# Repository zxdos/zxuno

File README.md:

# uGoph - gopher client for ZX-Uno(and possible other zx-spectrums)

## Requirements

For running you need:
 * ZX-Uno(or compatible) zx-spectrum clone with UART core
 * Stored WiFi creds via [.iwconfig](https://github.com/nihirash/iwconfig) utility.

For development you need only sjasmplus. 

Sadly, but there no emulator with ZX-Uno's UART.

## Supported features

Current version supports:

 * Rendering gopher-pages(catalogs)
 * Navigation between pages and servers
 * Rendering plain-text pages
 * Downloading binary files to SD card
 * Opening specified server(only by root path)

## Legals

(c) 2019 Alexander Sharikhin

This program is free software: you can redistribute it and/or modify
it under the terms of the GNU General Public License as published by
the Free Software Foundation, either version 3 of the License, or
(at your option) any later version.

This program is distributed in the hope that it will be useful,
but WITHOUT ANY WARRANTY; without even the implied warranty of
MERCHANTABILITY or FITNESS FOR A PARTICULAR PURPOSE.  See the
GNU General Public License for more details.

You should have received a copy of the GNU General Public License
along with this program.  If not, see <https://www.gnu.org/licenses/>.

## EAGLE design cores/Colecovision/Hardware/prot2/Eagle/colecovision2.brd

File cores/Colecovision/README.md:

# colecofpga
Colecovision FGPA port from old PACE project.

The original project information is here:
http://members.iinet.net.au/~msmcdoug/pace/Nanoboard/nanoboard.html

This project is a ColecoFPGA design port to the Terasic DE-1 and DE-2 development boards, ZX-Uno board and a stand-alone version with a EP2C5 Chinese board.

The Hardware folder is the Eagle project for the prototype. In Synth folder there are projects for all cards. The prototype 1 did not work and is abandoned, the project with the EP4C10 card is not completed.

The second prototype use SNES control to emulate all of the original joystick buttons. Holding TL button the original buttons simulate:

<pre>
Y      => 1
X      => 2
B      => 3
A      => 4
SELECT => 5
START  => 6
</pre>

Holding TR button the original buttons simulate:

<pre>
Y      => 7
X      => 8
B      => 9
A      => 0
SELECT => *
START  => #
</pre>

Holding START and SELECT together resets the machine, returning in the multcart menu.

The B button and Y (auto-fire) is the fire 1 of original joystick. The A button and X (auto-fire) is the fire 2.

For the DE-1, DE-2 and ZX-Uno boards the PS/2 keyboard emulates the original joystick:

The arrow keys simulate the original directional. Z key is the 'fire 1', X key is 'fire 2', 0-9 is '0-9', Q key is '*' and W key is '#'. ESC key resets the machine. For the ZX-Uno the joystick port also works for directionals and fire 1.

The key combination CTRL+ALT+BACKSPACE, on ZX-Uno version, reloads the main core of Xilinx, returning to the main menu.

In boards with VGA output (ZX-Uno), uses the HOME key to toggle VGA output.

In this circuit the BIOS ROM is loaded from the SD card as well as the ROM multcart. In the source folder 'SD_Card' contains all necessary files to the SD card. Format it to FAT16 and copy the files.

In multcart menu, use the directionals to navigate the ROMs and use FIRE 1 button to load the selected ROM.

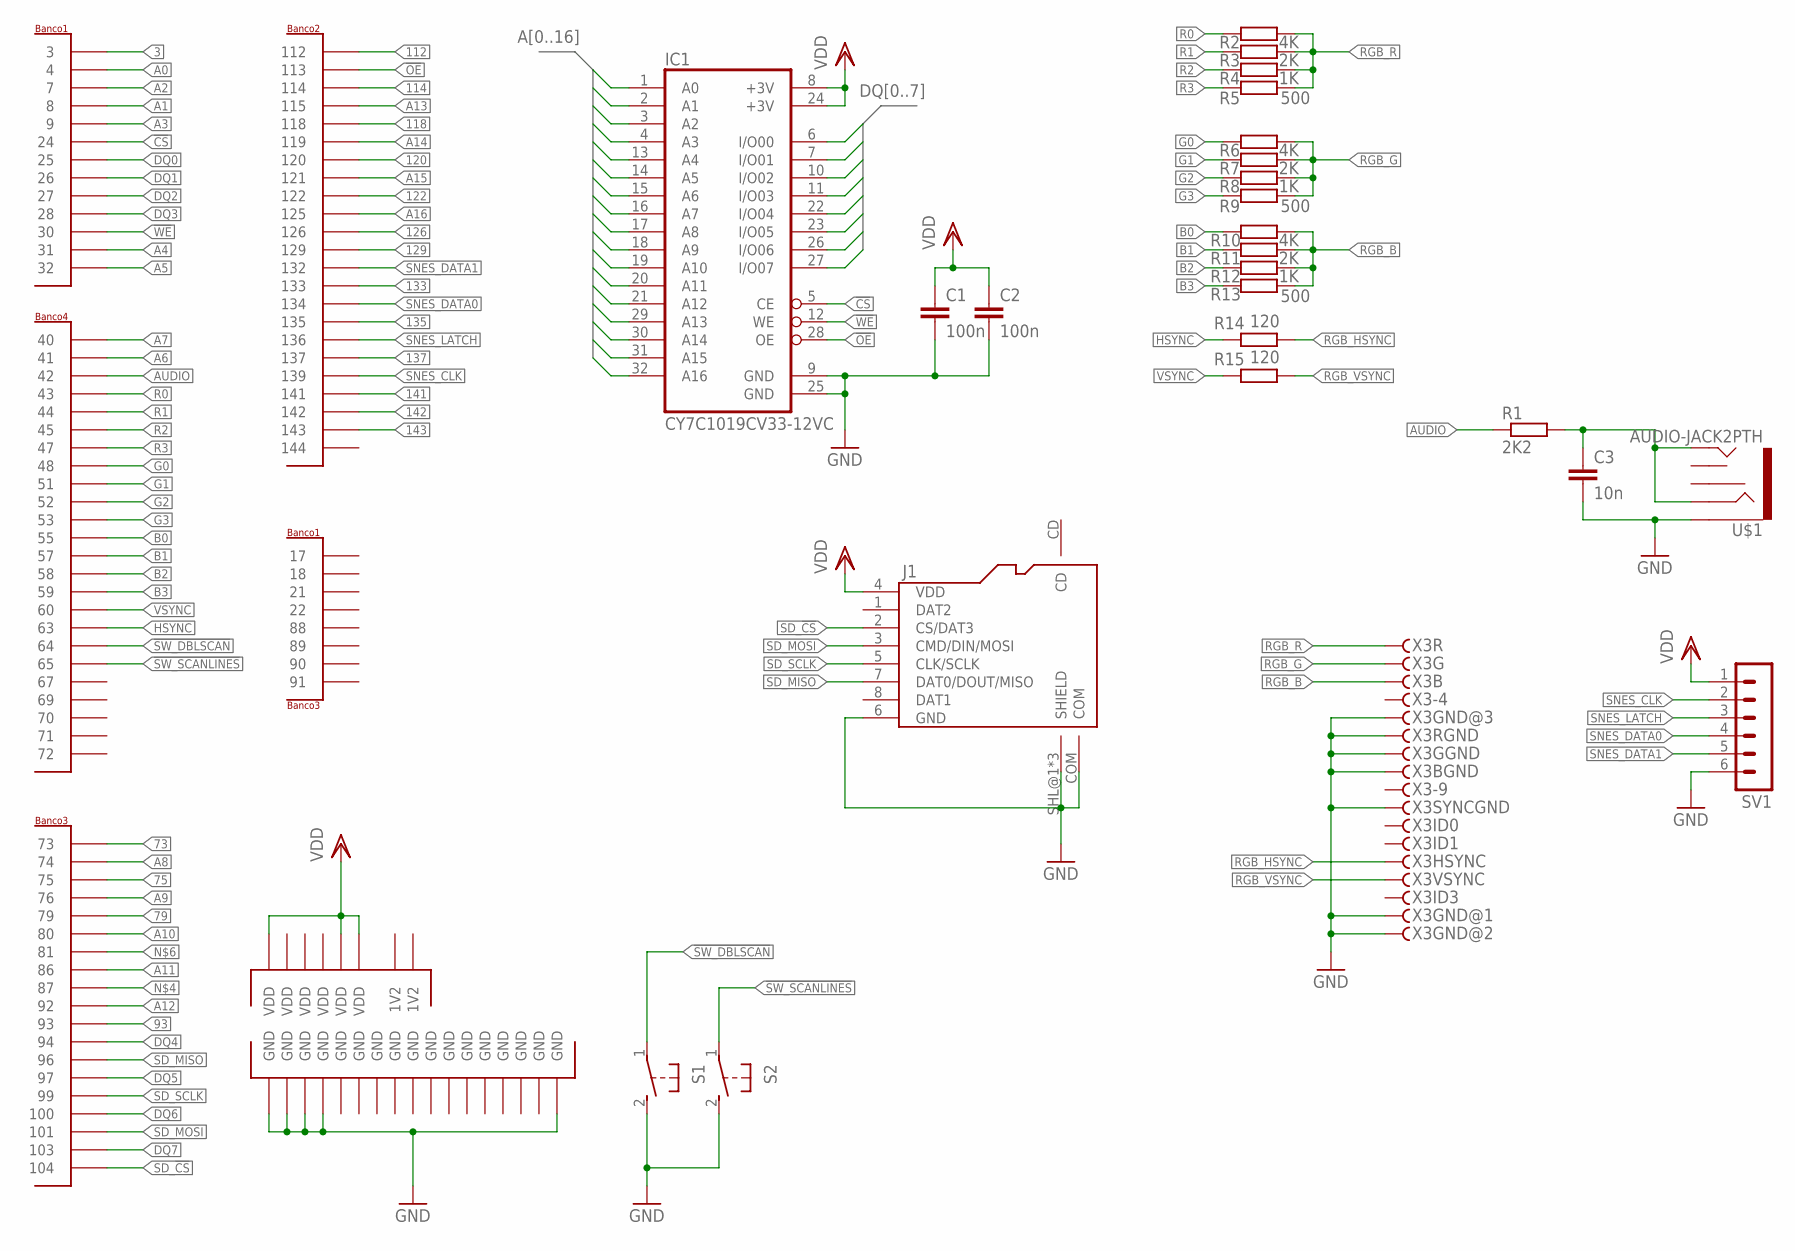
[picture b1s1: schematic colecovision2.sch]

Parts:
C1, C2: 100n; C1206
C3: 10n; C1206
IC1: CY7C1019CV33-12VC; SOJ32-400
J1: MICROSD-9P; 9P-SMD-W/-RING
PLC1: PLACAEP2C5LASER; 4X28_LASER
R1: 2K2; R1206
R2, R6, R10: 4K; R1206
R3, R7, R11: 2K; R1206
R4, R8, R12: 1K; R1206
R5, R9, R13: 500; R1206
R14, R15: 120; R1206
S1, S2: 31-XX; B3F-31XX
SV1: MA06-1
U$1: AUDIO-JACK2PTH; AUDIO-JACK
X3: VGAH; HDF15H

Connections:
1V2: PLC1.P$19 (1V2), PLC1.P$20 (1V2)
3: PLC1.P$3 (3)
73: PLC1.P$59 (73)
75: PLC1.P$61 (75)
79: PLC1.P$63 (79)
93: PLC1.P$73 (93)
112: PLC1.P$87 (112)
114: PLC1.P$89 (114)
118: PLC1.P$91 (118)
120: PLC1.P$93 (120)
122: PLC1.P$95 (122)
126: PLC1.P$97 (126)
129: PLC1.P$98 (129)
133: PLC1.P$100 (133)
135: PLC1.P$102 (135)
137: PLC1.P$104 (137)
141: PLC1.P$106 (141)
142: PLC1.P$107 (142)
143: PLC1.P$108 (143)
!CS: IC1.5 (CE), PLC1.P$16 (24)
!OE: IC1.28 (OE), PLC1.P$88 (113)
!SW_DBLSCAN: PLC1.P$46 (64), S1.1
!SW_SCANLINES: PLC1.P$47 (65), S2.1
!WE: IC1.12 (WE), PLC1.P$21 (30)
A0: IC1.1 (A0), PLC1.P$4 (4)
A1: IC1.2 (A1), PLC1.P$6 (8)
A2: IC1.3 (A2), PLC1.P$5 (7)
A3: IC1.4 (A3), PLC1.P$7 (9)
A4: IC1.13 (A4), PLC1.P$24 (31)
A5: IC1.14 (A5), PLC1.P$23 (32)
A6: IC1.15 (A6), PLC1.P$30 (41)
A7: IC1.16 (A7), PLC1.P$29 (40)
A8: IC1.17 (A8), PLC1.P$60 (74)
A9: IC1.18 (A9), PLC1.P$62 (76)
A10: IC1.19 (A10), PLC1.P$64 (80)
A11: IC1.20 (A11), PLC1.P$66 (86)
A12: IC1.21 (A12), PLC1.P$72 (92)
A13: IC1.29 (A13), PLC1.P$90 (115)
A14: IC1.30 (A14), PLC1.P$92 (119)
A15: IC1.31 (A15), PLC1.P$94 (121)
A16: IC1.32 (A16), PLC1.P$96 (125)
AUDIO: PLC1.P$31 (42), R1.1
B0: PLC1.P$40 (55), R10.1
B1: PLC1.P$41 (57), R11.1
B2: PLC1.P$42 (58), R12.1
B3: PLC1.P$43 (59), R13.1
DQ0: IC1.6 (I/O00), PLC1.P$15 (25)
DQ1: IC1.7 (I/O01), PLC1.P$18 (26)
DQ2: IC1.10 (I/O02), PLC1.P$17 (27)
DQ3: IC1.11 (I/O03), PLC1.P$22 (28)
DQ4: IC1.22 (I/O04), PLC1.P$74 (94)
DQ5: IC1.23 (I/O05), PLC1.P$76 (97)
DQ6: IC1.26 (I/O06), PLC1.P$78 (100)
DQ7: IC1.27 (I/O07), PLC1.P$80 (103)
G0: PLC1.P$36 (48), R6.1
G1: PLC1.P$37 (51), R7.1
G2: PLC1.P$38 (52), R8.1
G3: PLC1.P$39 (53), R9.1
GND: C1.2, C2.2, C3.2, IC1.9 (GND), IC1.25 (GND), J1.6 (GND), J1.COM, J1.SHL@1 (SHIELD), J1.SHL@2 (SHIELD), J1.SHL@3 (SHIELD), PLC1.P$1 (GND), PLC1.P$2 (GND), PLC1.P$8 (GND), PLC1.P$9 (GND), PLC1.P$10 (GND), PLC1.P$25 (GND), PLC1.P$26 (GND), PLC1.P$53 (GND), PLC1.P$54 (GND), PLC1.P$57 (GND), PLC1.P$58 (GND), PLC1.P$82 (GND), PLC1.P$83 (GND), PLC1.P$85 (GND), PLC1.P$86 (GND), PLC1.P$110 (GND), PLC1.P$111 (GND), S1.2 (S), S2.2 (S), SV1.6, U$1.SLEEVE, X3.5, X3.6, X3.7, X3.8, X3.10, X3.GND@1, X3.GND@2
HSYNC: PLC1.P$45 (63), R14.1
unnamed: C3.1, R1.2, U$1.RING, U$1.TIP
R0: PLC1.P$32 (43), R2.1
R1: PLC1.P$33 (44), R3.1
R2: PLC1.P$34 (45), R4.1
R3: PLC1.P$35 (47), R5.1
RGB_B: R10.2, R11.2, R12.2, R13.2, X3.3
RGB_G: R6.2, R7.2, R8.2, R9.2, X3.2
RGB_HSYNC: R14.2, X3.13
RGB_R: R2.2, R3.2, R4.2, R5.2, X3.1
RGB_VSYNC: R15.2, X3.14
SD_!CS: J1.2 (CS/DAT3), PLC1.P$81 (104)
SD_MISO: J1.7 (DAT0/DOUT/MISO), PLC1.P$75 (96)
SD_MOSI: J1.3 (CMD/DIN/MOSI), PLC1.P$79 (101)
SD_SCLK: J1.5 (CLK/SCLK), PLC1.P$77 (99)
SNES_CLK: PLC1.P$105 (139), SV1.2
SNES_DATA0: PLC1.P$101 (134), SV1.4
SNES_DATA1: PLC1.P$99 (132), SV1.5
SNES_LATCH: PLC1.P$103 (136), SV1.3
VDD: C1.1, C2.1, IC1.8 (+3V), IC1.24 (+3V), J1.4 (VDD), PLC1.P$27 (VDD), PLC1.P$28 (VDD), PLC1.P$55 (VDD), PLC1.P$56 (VDD), PLC1.P$84 (VDD), PLC1.P$112 (VDD), SV1.1
VSYNC: PLC1.P$44 (60), R15.1

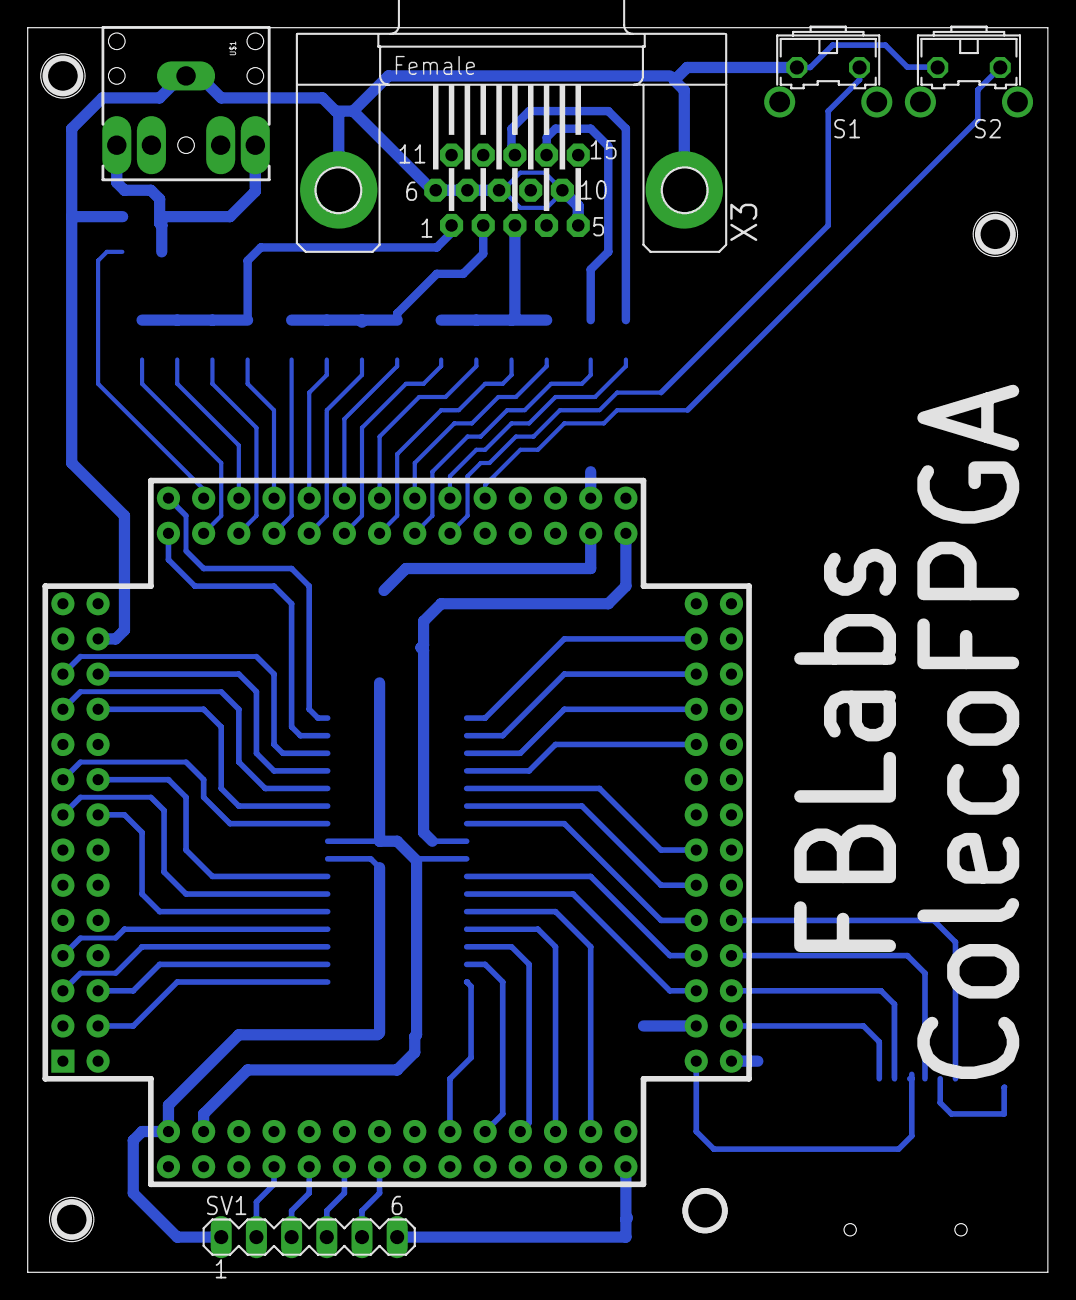
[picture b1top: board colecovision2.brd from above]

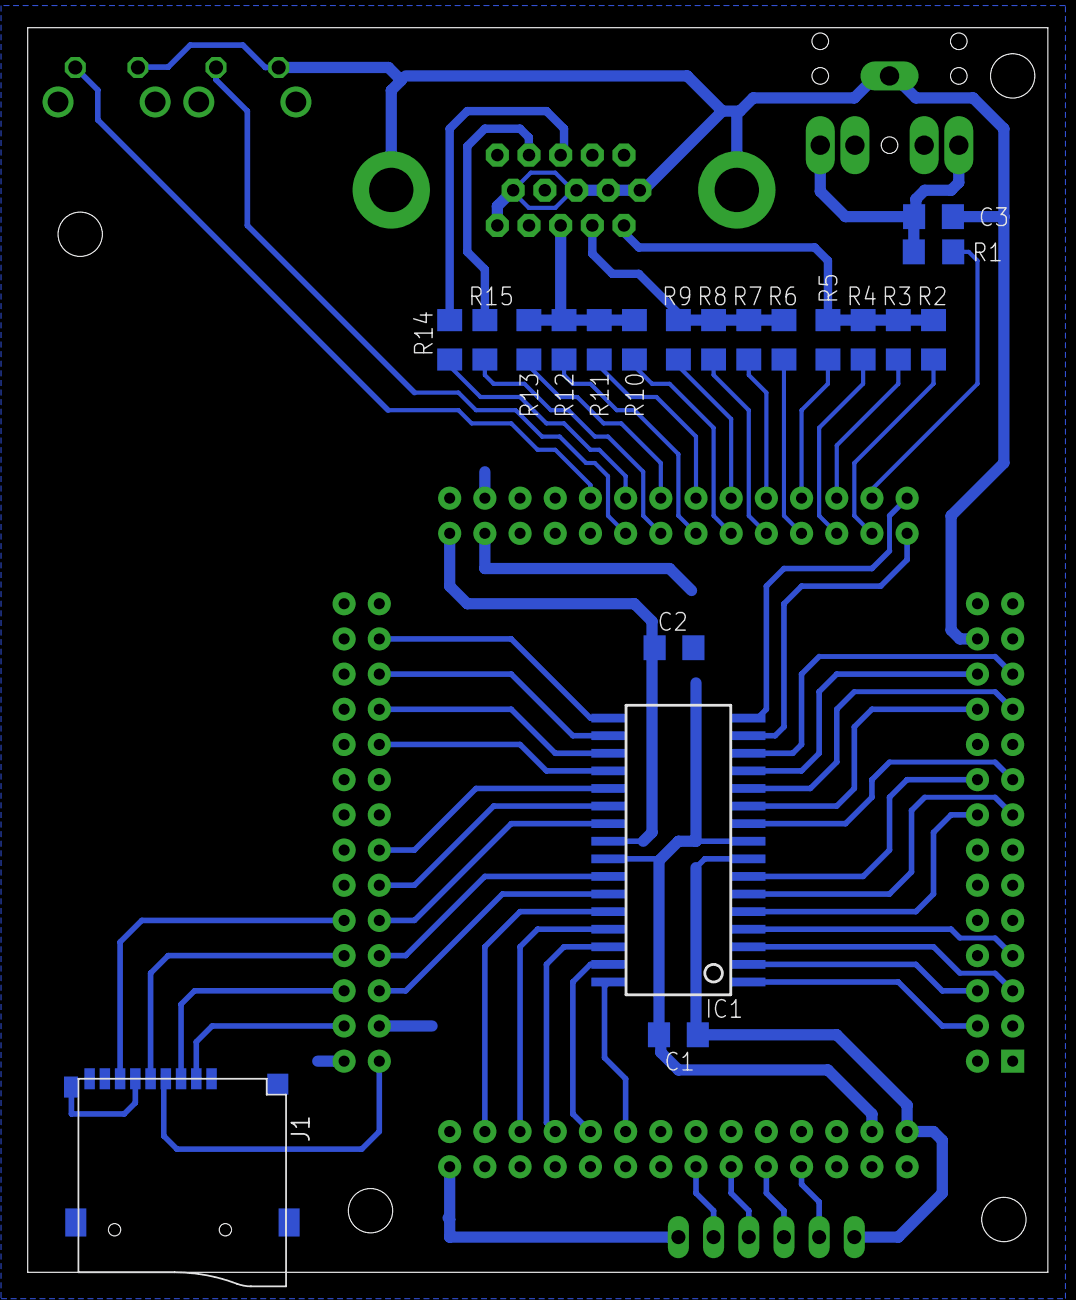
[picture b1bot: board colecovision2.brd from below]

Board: 3 copper layers, 73.6 x 89.8 mm, 26 parts (20 on the bottom side), 62 nets.

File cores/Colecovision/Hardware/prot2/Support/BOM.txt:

Compra:

Qty Value             Device            Package        Parts       Description
------------------------------------------------------------------------------------------------------------
1   PLACAEP2C5LASER   PLACAEP2C5LASER   4X28_LASER     PLC1        Placa EP2C5
1   CY7C1019CV33-12VC CY7C1019CV33-12VC SOJ32-400      IC1         128K x 8 Static RAM 10ns
2   120               R-EU_R1206        R1206          R14, R15    RESISTOR, European symbol
3   1K                R-EU_R1206        R1206          R4, R8, R12 RESISTOR, European symbol
3   2K                R-EU_R1206        R1206          R3, R7, R11 RESISTOR, European symbol
1   2K2               R-EU_R1206        R1206          R1          RESISTOR, European symbol
3   4K                R-EU_R1206        R1206          R2, R6, R10 RESISTOR, European symbol
3   500               R-EU_R1206        R1206          R5, R9, R13 RESISTOR, European symbol
2   100n              C-EUC1206         C1206          C1, C2      CAPACITOR, European symbol
1   10n               C-EUC1206         C1206          C3          CAPACITOR, European symbol
1                     MICROSD-9P        9P-SMD-W/-RING J1          Micro SD 9 pins
1                     VGAH              HDF15H         X3          SUB-D
1   AUDIO-JACK2PTH    AUDIO-JACK2PTH    AUDIO-JACK     U$1         Stereo audio jack with bypass switches.
2                     31-XX             B3F-31XX       S1, S2      OMRON SWITCH
1                     MA06-1            MA06-1         SV1         PIN HEADER


Montagem:

Part Value             Device            Package        Description
------------------------------------------------------------------------------------------------------------
PLC1 PLACAEP2C5LASER   PLACAEP2C5LASER   4X28_LASER     Placa EP2C5
IC1  CY7C1019CV33-12VC CY7C1019CV33-12VC SOJ32-400      128K x 8 Static RAM 10ns
R1   2K2               R-EU_R1206        R1206          RESISTOR, European symbol
R2   4K                R-EU_R1206        R1206          RESISTOR, European symbol
R3   2K                R-EU_R1206        R1206          RESISTOR, European symbol
R4   1K                R-EU_R1206        R1206          RESISTOR, European symbol
R5   500               R-EU_R1206        R1206          RESISTOR, European symbol
R6   4K                R-EU_R1206        R1206          RESISTOR, European symbol
R7   2K                R-EU_R1206        R1206          RESISTOR, European symbol
R8   1K                R-EU_R1206        R1206          RESISTOR, European symbol
R9   500               R-EU_R1206        R1206          RESISTOR, European symbol
R10  4K                R-EU_R1206        R1206          RESISTOR, European symbol
R11  2K                R-EU_R1206        R1206          RESISTOR, European symbol
R12  1K                R-EU_R1206        R1206          RESISTOR, European symbol
R13  500               R-EU_R1206        R1206          RESISTOR, European symbol
R14  120               R-EU_R1206        R1206          RESISTOR, European symbol
R15  120               R-EU_R1206        R1206          RESISTOR, European symbol
C1   100n              C-EUC1206         C1206          CAPACITOR, European symbol
C2   100n              C-EUC1206         C1206          CAPACITOR, European symbol
C3   10n               C-EUC1206         C1206          CAPACITOR, European symbol
U$1  AUDIO-JACK2PTH    AUDIO-JACK2PTH    AUDIO-JACK     Stereo audio jack with bypass switches.
J1                     MICROSD-9P        9P-SMD-W/-RING Micro SD 9 pins
X3                     VGAH              HDF15H         SUB-D
S1                     31-XX             B3F-31XX       OMRON SWITCH
S2                     31-XX             B3F-31XX       OMRON SWITCH
SV1                    MA06-1            MA06-1         PIN HEADER

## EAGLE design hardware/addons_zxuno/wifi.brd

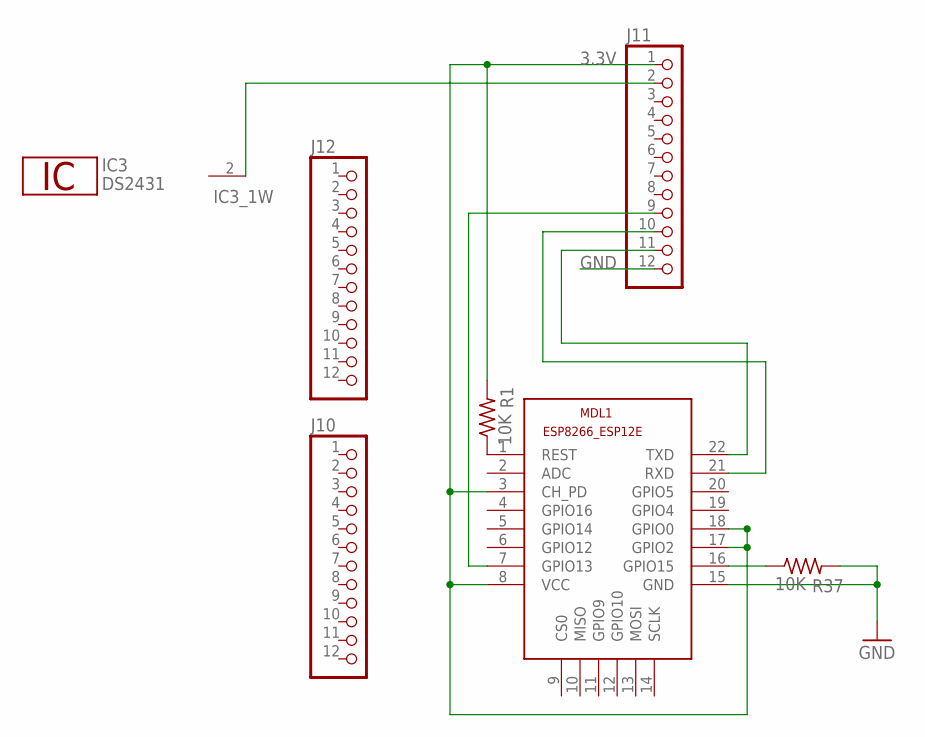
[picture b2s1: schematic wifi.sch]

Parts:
IC3: DS2431; TO92-
J10, J11, J12: PINHD-1X12; 1X12
MDL1: ESP8266-12EESP8266-ESP12E; ESP8266-ESP12E
R1, R37: 10K; R0805

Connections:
3.3V: J11.1, MDL1.3 (CH_PD), MDL1.8 (VCC), MDL1.17 (GPIO2), MDL1.18 (GPIO0), R1.2
GND: IC3.1 (GND), J11.12, MDL1.15 (GND), R37.2
unnamed: MDL1.16 (GPIO15), R37.1
unnamed: J11.9, MDL1.7 (GPIO13)
unnamed: J11.10, MDL1.21 (RXD)
unnamed: J11.11, MDL1.22 (TXD)
unnamed: MDL1.1 (REST), R1.1
unnamed: IC3.2 (1W), J11.2

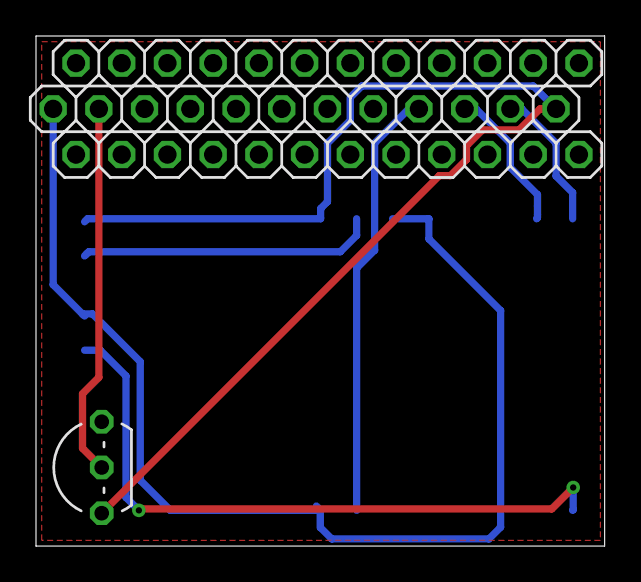
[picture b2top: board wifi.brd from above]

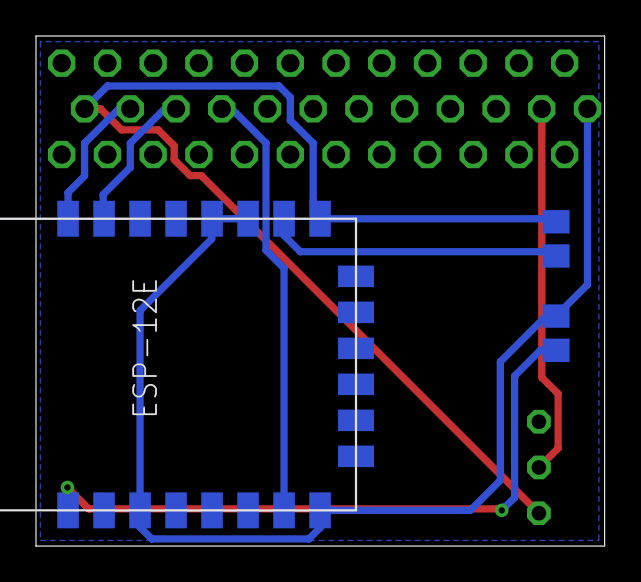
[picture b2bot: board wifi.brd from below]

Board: 2 copper layers, 31.6 x 28.3 mm, 7 parts (3 on the bottom side), 8 nets.

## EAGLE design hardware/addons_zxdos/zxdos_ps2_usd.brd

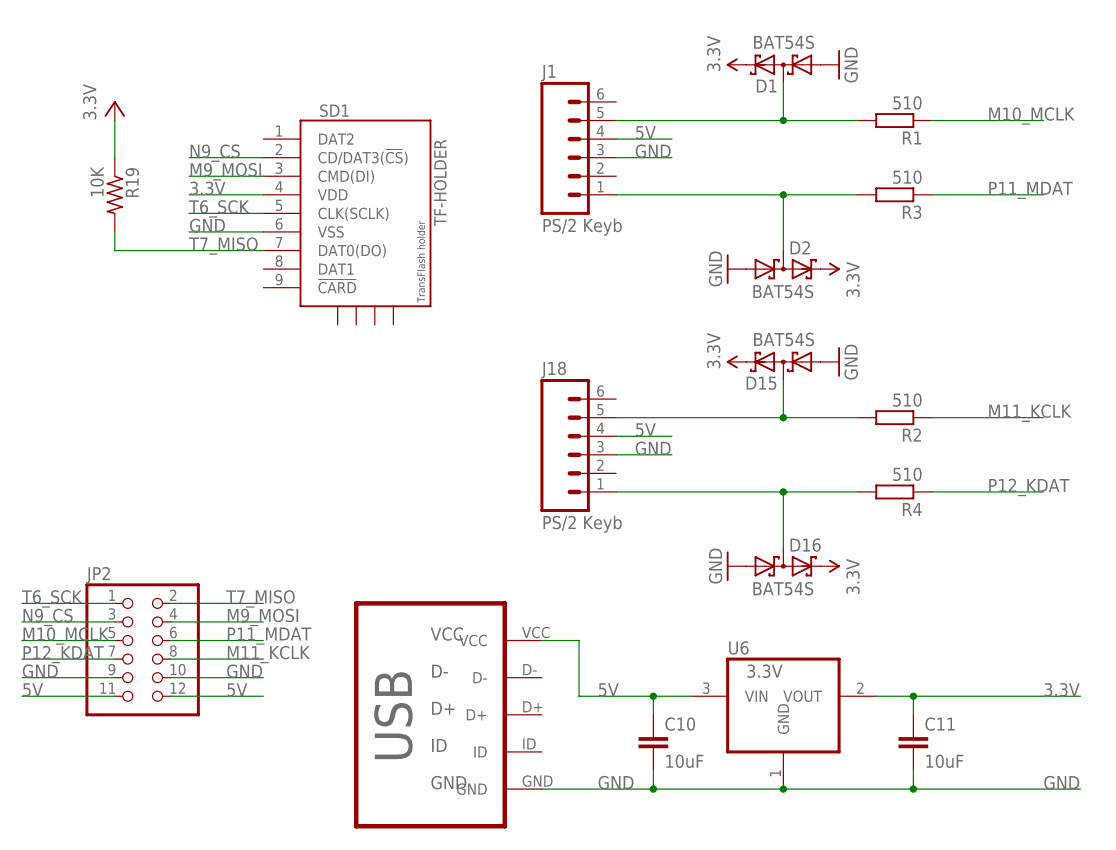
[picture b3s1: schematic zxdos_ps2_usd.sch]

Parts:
C10, C11: 10uF; C0805K
D1, D2, D15, D16: BAT54S; SOT23
J1, J18: PS/2 Keyb; DINC/MIN_TM/6_1PRIMARY
J17: MICRO-USB-B; MICRO_USB_4_LEGS
JP2: PINHD-2X6; 2X06
R1, R2, R3, R4: 510; R0805
R19: 10K; R0805
SD1: TF-HOLDER; TF-PULL
U6: 3.3V; SOT223

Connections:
3.3V: C11.1, D1.2 (C2), D2.2 (C2), D15.2 (C2), D16.2 (C2), R19.1, SD1.4 (VDD), U6.2 (VOUT)
5V: C10.1, J1.4, J17.VCC, J18.4, JP2.11, JP2.12, U6.3 (VIN)
GND: C10.2, C11.2, D1.1 (A1), D2.1 (A1), D15.1 (A1), D16.1 (A1), J1.3, J17.GND, J18.3, JP2.9, JP2.10, SD1.6 (VSS), U6.1 (GND)
M9_MOSI: JP2.4, SD1.3 (CMD(DI))
M10_MCLK: JP2.5, R1.1
M11_KCLK: JP2.8, R2.1
N9_CS: JP2.3, SD1.2 (CD/DAT3(!CS!))
unnamed: D1.3 (C1A2), J1.5, R1.2
unnamed: D2.3 (C1A2), J1.1, R3.2
unnamed: D15.3 (C1A2), J18.5, R2.2
unnamed: D16.3 (C1A2), J18.1, R4.2
P11_MDAT: JP2.6, R3.1
P12_KDAT: JP2.7, R4.1
T6_SCK: JP2.1, SD1.5 (CLK(SCLK))
T7_MISO: JP2.2, R19.2, SD1.7 (DAT0(DO))

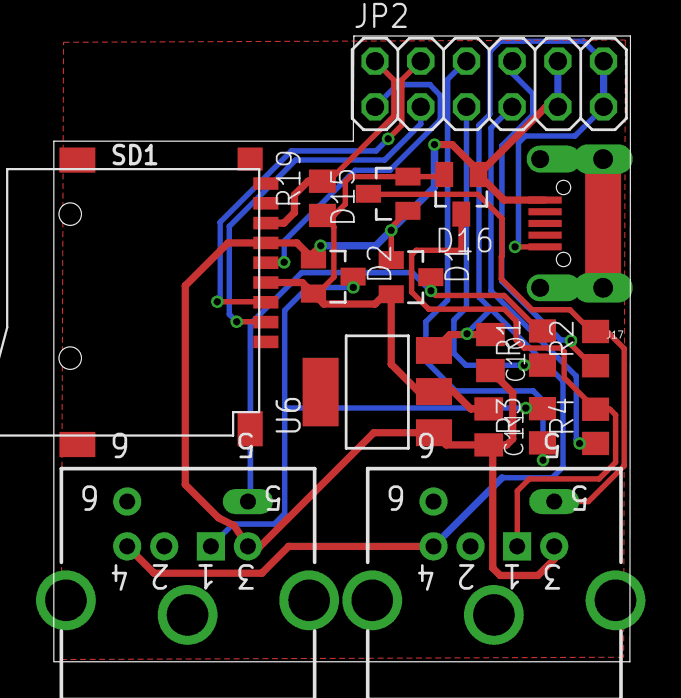
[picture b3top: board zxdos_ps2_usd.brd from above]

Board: 2 copper layers, 32.0 x 34.8 mm, 17 parts (0 on the bottom side), 15 nets.

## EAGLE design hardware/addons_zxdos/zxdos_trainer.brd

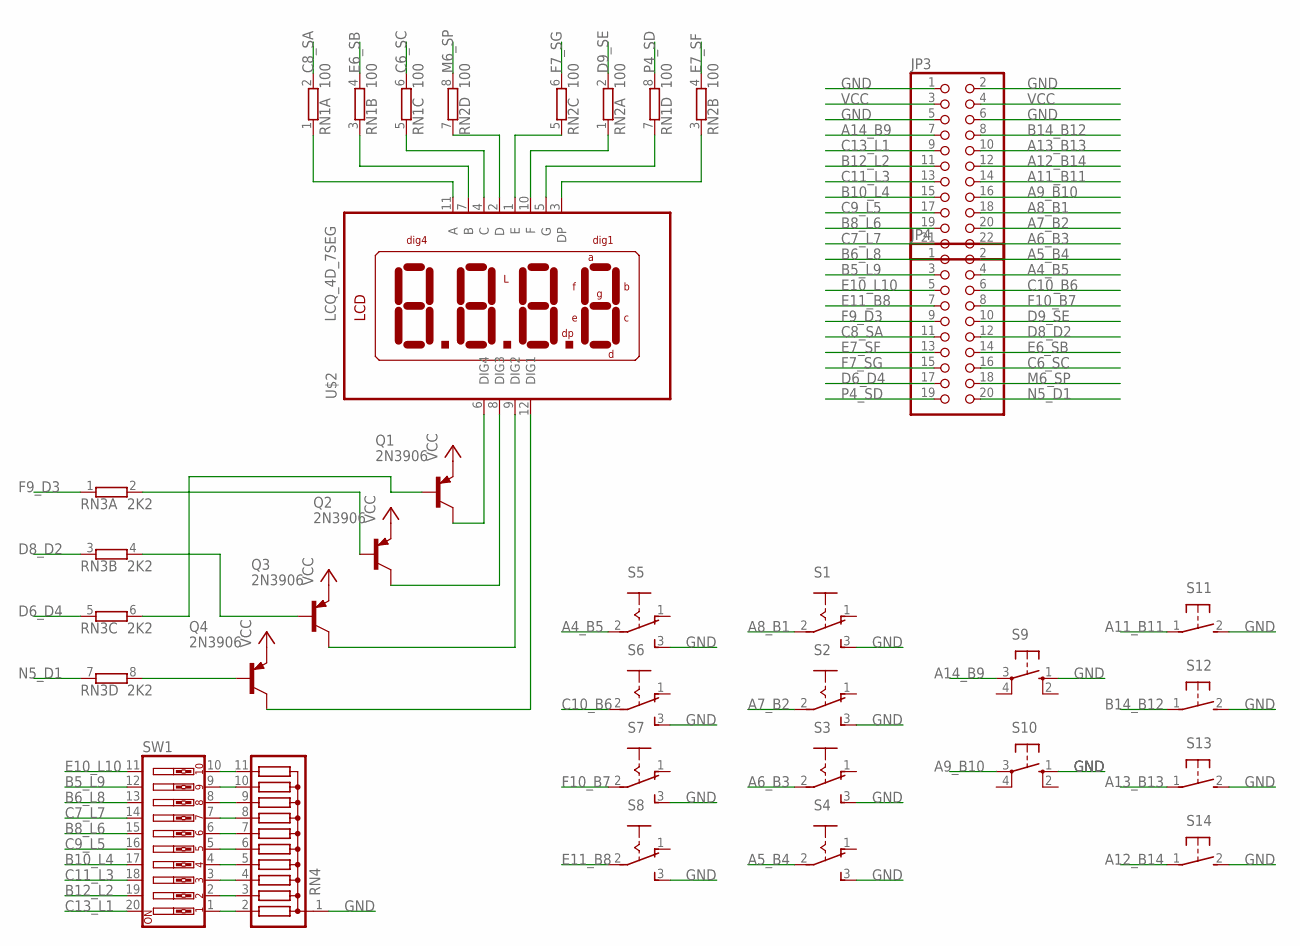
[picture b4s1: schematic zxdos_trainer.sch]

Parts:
JP3: PINHD-2X11; 2X11
JP4: PINHD-2X10; 2X10
Q1, Q2, Q3, Q4: 2N3906; TO92
RN1, RN2: 100; SIL8
RN3: 2K2; SIL8
RN4: G10R; SIL11
S1, S2, S3, S4, S5, S6, S7, S8: M251
S9, S10: 10-XX; B3F-10XX
S11, S12, S13, S14: 31-XX; B3F-31XX
SW1: SW_DIP-10; EDG-10
U$2: LCQ_4D_7SEG; LDQ_4D_7SEG

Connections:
A4_B5: JP4.4, S5.2
A5_B4: JP4.2, S4.2
A6_B3: JP3.22, S3.2
A7_B2: JP3.20, S2.2
A8_B1: JP3.18, S1.2
A9_B10: JP3.16, S10.3
A11_B11: JP3.14, S11.1
A12_B14: JP3.12, S14.1
A13_B13: JP3.10, S13.1
A14_B9: JP3.7, S9.3
B5_L9: JP4.3, SW1.12
B6_L8: JP4.1, SW1.13
B8_L6: JP3.19, SW1.15
B10_L4: JP3.15, SW1.17
B12_L2: JP3.11, SW1.19
B14_B12: JP3.8, S12.1
C6_SC: JP4.16, RN1.6 (2)
C7_L7: JP3.21, SW1.14
C8_SA: JP4.11, RN1.2
C9_L5: JP3.17, SW1.16
C10_B6: JP4.6, S6.2
C11_L3: JP3.13, SW1.18
C13_L1: JP3.9, SW1.20
D6_D4: JP4.17, RN3.5 (1)
D8_D2: JP4.12, RN3.3 (1)
D9_SE: JP4.10, RN2.2
E6_SB: JP4.14, RN1.4 (2)
E7_SF: JP4.13, RN2.4 (2)
E10_L10: JP4.5, SW1.11
E11_B8: JP4.7, S8.2
F7_SG: JP4.15, RN2.6 (2)
F9_D3: JP4.9, RN3.1
F10_B7: JP4.8, S7.2
GND: JP3.1, JP3.2, JP3.5, JP3.6, RN4.1, S1.3 (S), S2.3 (S), S3.3 (S), S4.3 (S), S5.3 (S), S6.3 (S), S7.3 (S), S8.3 (S), S9.1 (S), S10.1 (S), S11.2 (S), S12.2 (S), S13.2 (S), S14.2 (S)
M6_SP: JP4.18, RN2.8 (2)
N5_D1: JP4.20, RN3.7 (1)
unnamed: RN4.2, SW1.1
unnamed: RN4.3, SW1.2
unnamed: Q1.1 (C), U$2.6 (DIG4)
unnamed: RN4.4, SW1.3
unnamed: Q2.1 (C), U$2.8 (DIG3)
unnamed: Q3.1 (C), U$2.9 (DIG2)
unnamed: RN4.5, SW1.4
unnamed: Q4.1 (C), U$2.12 (DIG1)
unnamed: Q4.2 (B), RN3.8 (2)
unnamed: RN1.1, U$2.11 (A)
unnamed: RN1.3 (1), U$2.7 (B)
unnamed: RN1.5 (1), U$2.4 (C)
unnamed: RN2.7 (1), U$2.2 (D)
unnamed: RN2.5 (1), U$2.1 (E)
unnamed: RN2.1, U$2.10 (F)
unnamed: Q2.2 (B), RN3.2
unnamed: RN2.3 (1), U$2.3 (DP)
unnamed: Q1.2 (B), RN3.6 (2)
unnamed: RN1.7 (1), U$2.5 (G)
unnamed: Q3.2 (B), RN3.4 (2)
unnamed: RN4.6, SW1.5
unnamed: RN4.7, SW1.6
unnamed: RN4.8, SW1.7
unnamed: RN4.9, SW1.8
unnamed: RN4.10, SW1.9
unnamed: RN4.11, SW1.10
P4_SD: JP4.19, RN1.8 (2)
VCC: JP3.3, JP3.4, Q1.3 (E), Q2.3 (E), Q3.3 (E), Q4.3 (E)

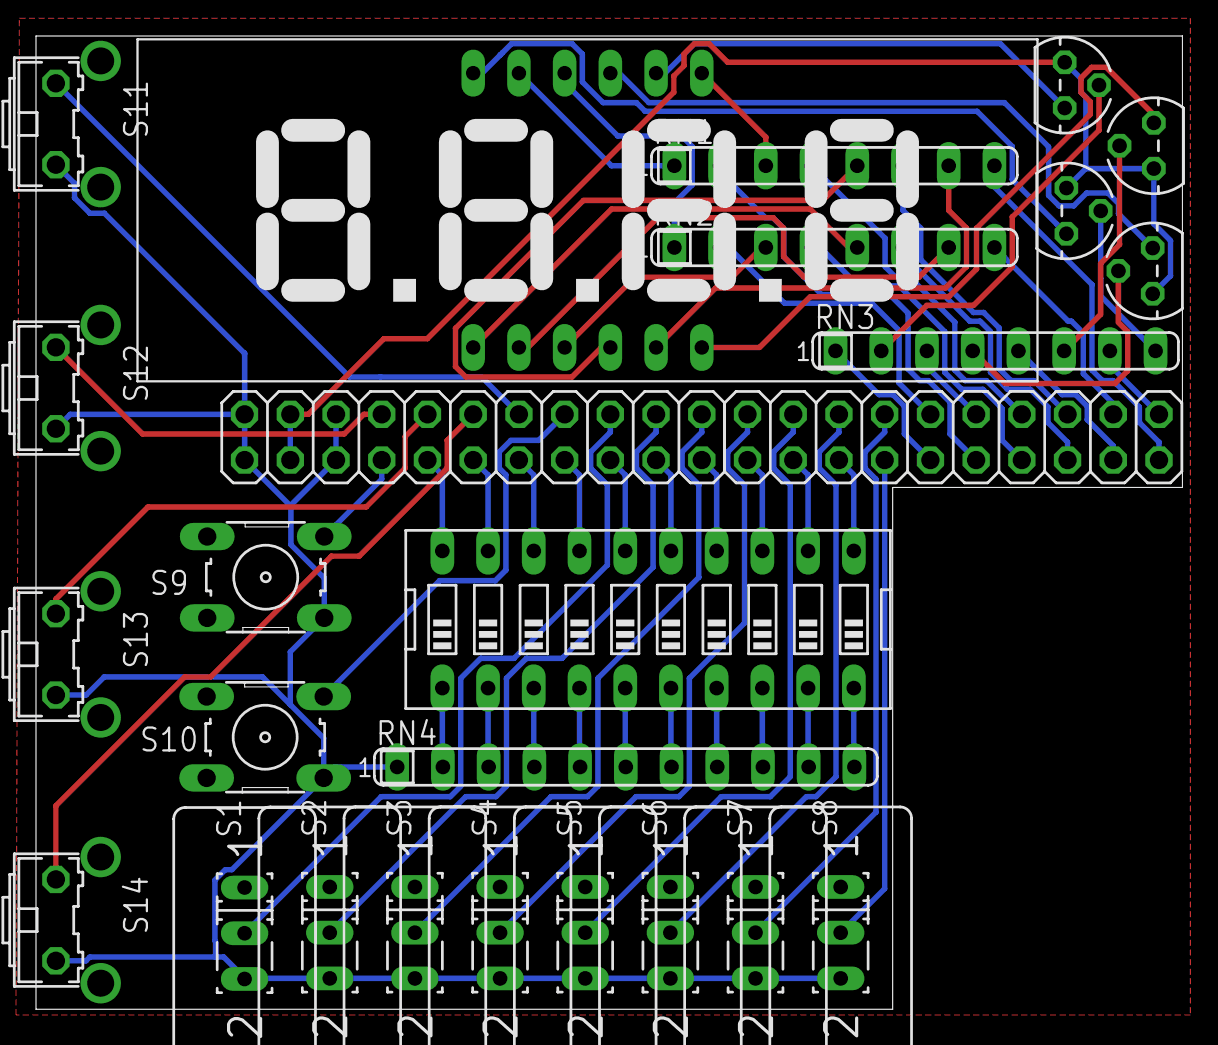
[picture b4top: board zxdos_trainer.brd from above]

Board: 2 copper layers, 63.7 x 54.1 mm, 26 parts (0 on the bottom side), 64 nets.

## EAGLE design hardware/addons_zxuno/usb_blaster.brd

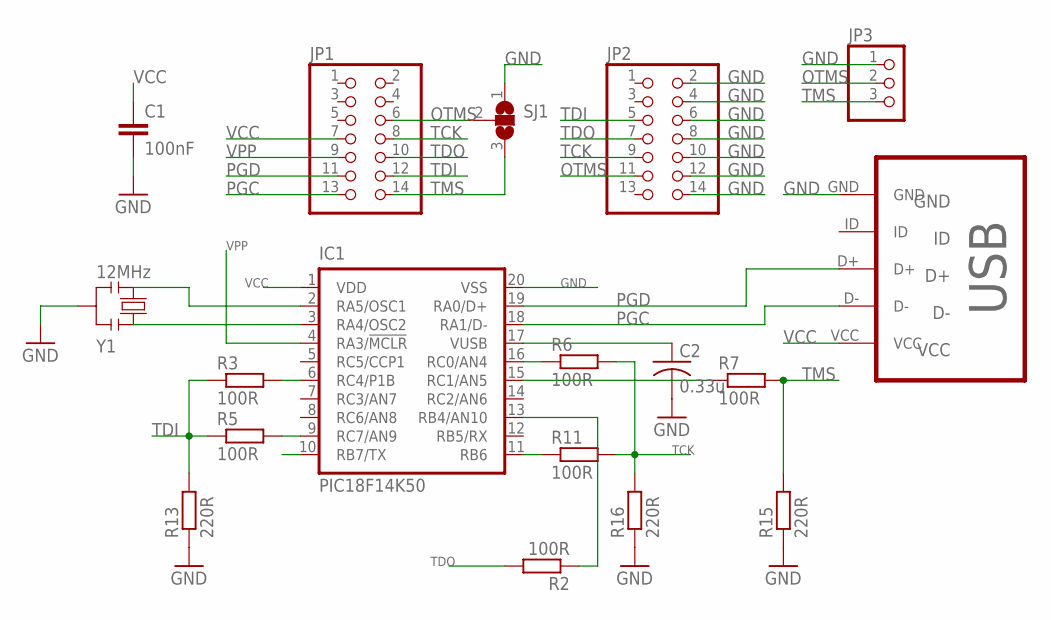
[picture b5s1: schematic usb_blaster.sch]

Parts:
C1: 100nF; C0805
C2: 0.33u; C0805
IC1: PIC18F14K50; SS20
JP1, JP2: PINHD-2X7; 2X07
JP3: PINHD-1X3; 1X03
R2, R3, R5, R6, R7, R11: 100R; R0805
R13, R15, R16: 220R; R0805
SJ1: SJ2W; SJ_2
U$2: MICRO-USB-B; MICRO_USB_4_LEGS
Y1: 12MHz; RESONATOR

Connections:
GND: C1.2, C2.2, IC1.20 (VSS), JP2.2, JP2.4, JP2.6, JP2.8, JP2.10, JP2.12, JP2.14, JP3.1, R13.1, R15.1, R16.1, SJ1.1, U$2.GND, Y1.2
unnamed: IC1.2 (RA5/OSC1), Y1.3
unnamed: IC1.9 (RC7/AN9), R5.2
unnamed: IC1.6 (RC4/P1B), R3.2
unnamed: IC1.11 (RB6), R11.1
unnamed: IC1.16 (RC0/AN4), R6.1
unnamed: IC1.13 (RB4/AN10), R2.1
unnamed: IC1.15 (RC1/AN5), R7.1
unnamed: IC1.3 (RA4/OSC2), Y1.1
unnamed: C2.1, IC1.17 (VUSB)
OTMS: JP1.6, JP2.11, JP3.2, SJ1.2
PGC: IC1.18 (RA1/D-), JP1.13, U$2.D-
PGD: IC1.19 (RA0/D+), JP1.11, U$2.D+
TCK: JP1.8, JP2.9, R6.2, R11.2, R16.2
TDI: JP1.12, JP2.5, R3.1, R5.1, R13.2
TDO: JP1.10, JP2.7, R2.2
TMS: JP1.14, JP3.3, R7.2, R15.2, SJ1.3
VCC: C1.1, IC1.1 (VDD), JP1.7, U$2.VCC
VPP: IC1.4 (RA3/!MCLR!), JP1.9

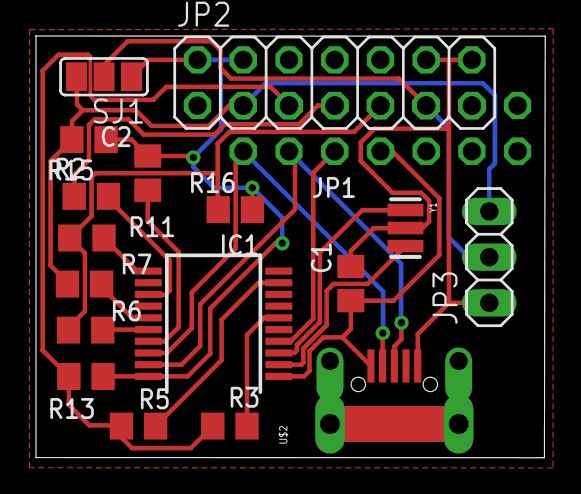
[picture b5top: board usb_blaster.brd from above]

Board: 2 copper layers, 28.3 x 23.4 mm, 18 parts (1 on the bottom side), 19 nets.

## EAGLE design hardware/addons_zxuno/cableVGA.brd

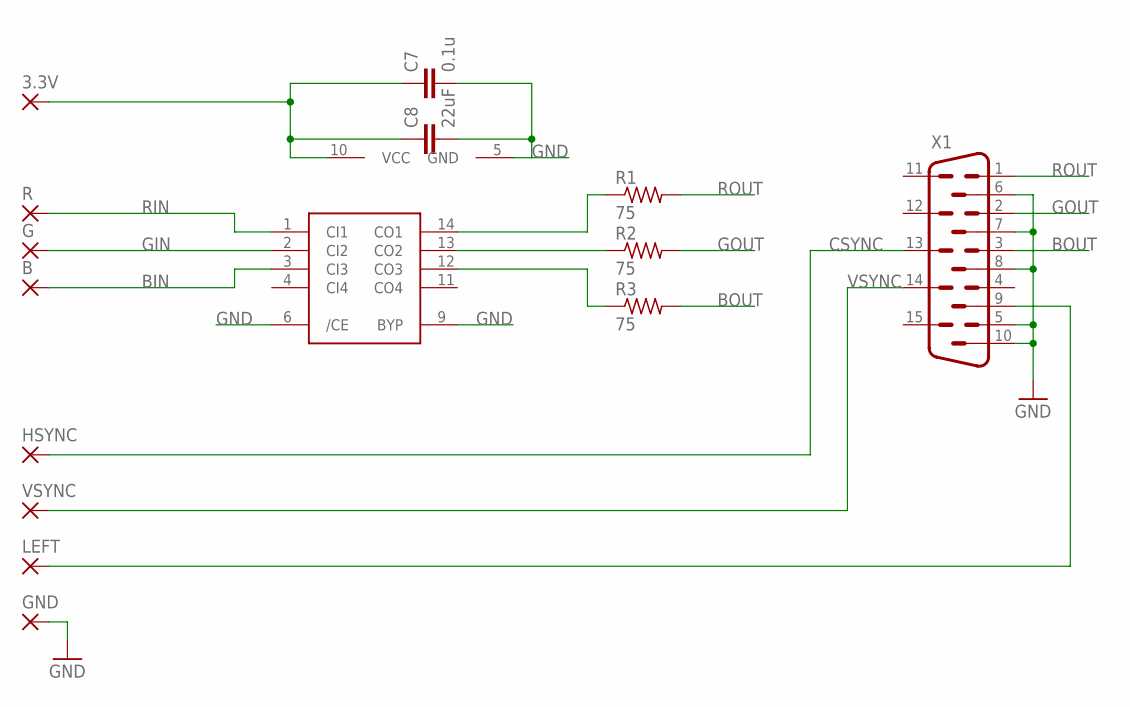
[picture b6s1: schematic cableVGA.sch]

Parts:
3.3V: WIREPADSMD2,54-5,08; SMD2,54-5,08
B: WIREPADSMD2,54-5,08; SMD2,54-5,08
C7: 0.1u; C0805K
C8: 22uF; C0805K
G: WIREPADSMD2,54-5,08; SMD2,54-5,08
GND: WIREPADSMD2,54-5,08; SMD2,54-5,08
HSYNC: WIREPADSMD2,54-5,08; SMD2,54-5,08
LEFT: WIREPADSMD2,54-5,08; SMD2,54-5,08
R: WIREPADSMD2,54-5,08; SMD2,54-5,08
R1, R2, R3: 75; R0805
U$2: THS7374
VSYNC: WIREPADSMD2,54-5,08; SMD2,54-5,08
X1: HM15H; HDM15H

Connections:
3.3V: 3.3V.1, C7.1, C8.1, U$2.10 (VCC)
BIN: B.1, U$2.3 (CI3)
BOUT: R3.2, X1.3
CSYNC: HSYNC.1, X1.13
GIN: G.1, U$2.2 (CI2)
GND: C7.2, C8.2, GND.1, U$2.5 (GND), U$2.6 (/CE), U$2.9 (BYP), X1.5, X1.6, X1.7, X1.8, X1.10
GOUT: R2.2, X1.2
LEFT: LEFT.1, X1.9
unnamed: R2.1, U$2.13 (CO2)
unnamed: R1.1, U$2.14 (CO1)
unnamed: R3.1, U$2.12 (CO3)
RIN: R.1, U$2.1 (CI1)
ROUT: R1.2, X1.1
VSYNC: VSYNC.1, X1.14

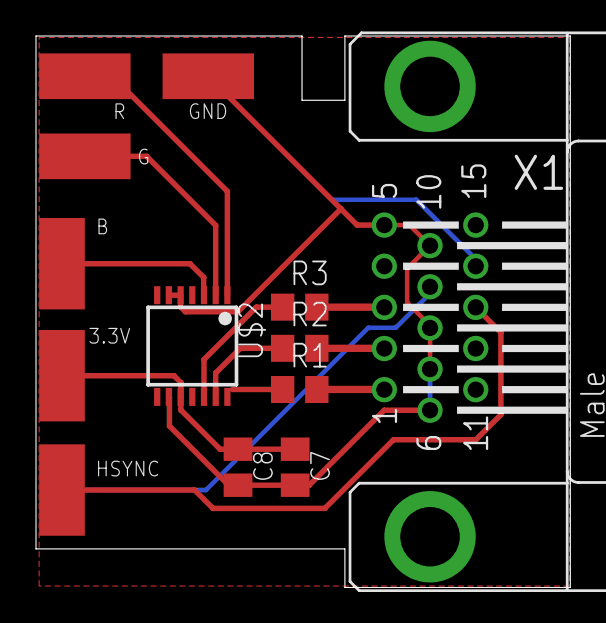
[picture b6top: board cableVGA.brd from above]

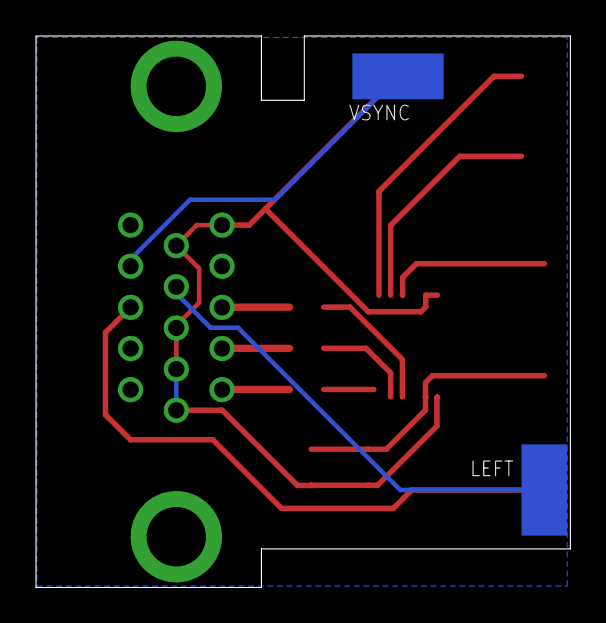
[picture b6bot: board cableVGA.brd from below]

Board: 2 copper layers, 29.7 x 30.6 mm, 15 parts (2 on the bottom side), 14 nets.

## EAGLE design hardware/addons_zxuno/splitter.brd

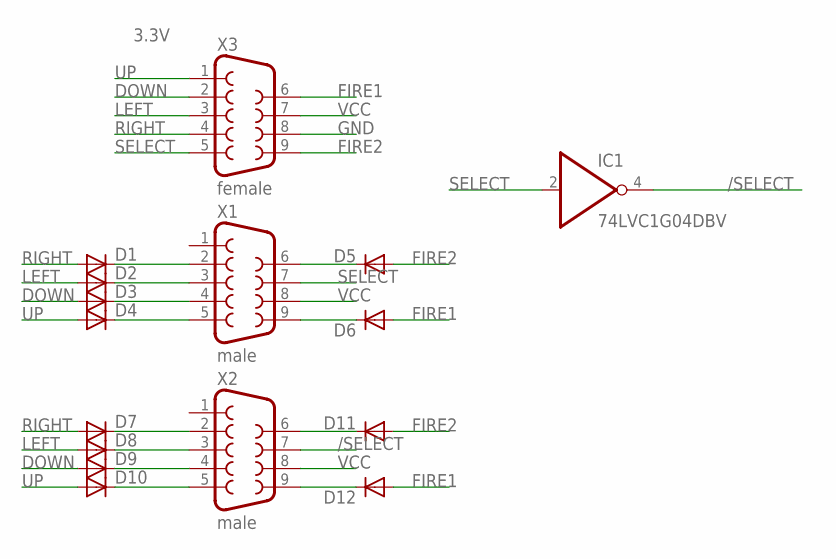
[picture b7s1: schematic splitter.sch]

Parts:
D1, D2, D3, D4, D5, D6, D7, D8, D9, D10, D11, D12: DIODE-SOD323-R; SOD323-R
IC1: 74LVC1G04DBV; SOT23-5
X1, X2: male; F09D
X3: female; F09D

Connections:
/SELECT: IC1.4 (O), X2.7
DOWN: D3.A, D9.A, X3.2
FIRE1: D6.A, D12.A, X3.6
FIRE2: D5.A, D11.A, X3.9
GND: IC1.3 (GND), X3.8
LEFT: D2.A, D8.A, X3.3
unnamed: D2.C, X1.3
unnamed: D8.C, X2.3
unnamed: D1.C, X1.2
unnamed: D3.C, X1.4
unnamed: D7.C, X2.2
unnamed: D9.C, X2.4
unnamed: D10.C, X2.5
unnamed: D4.C, X1.5
unnamed: D6.C, X1.9
unnamed: D5.C, X1.6
unnamed: D12.C, X2.9
unnamed: D11.C, X2.6
RIGHT: D1.A, D7.A, X3.4
SELECT: IC1.2 (I), X1.7, X3.5
UP: D4.A, D10.A, X3.1
VCC: IC1.5 (VCC), X1.8, X2.8, X3.7

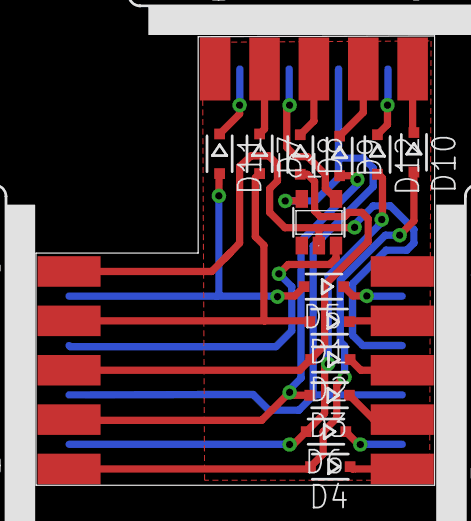
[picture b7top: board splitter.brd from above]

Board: 2 copper layers, 22.1 x 25.0 mm, 16 parts (0 on the bottom side), 22 nets.

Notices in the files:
hardware/addons_zxuno/sram.brd:
(C)2017 ZXUno Team
